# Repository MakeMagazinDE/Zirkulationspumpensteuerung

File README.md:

Maker Media GmbH

# Warmwasser-Sparpumpe

## für Heizkessel mit Zirkulationskreislauf

Heizkessel mit Brauchwasser-Erwärmung sind in der Regel mit einer Pumpe für den Warmwasser-Zirkulationskreislauf ausgerüstet, die regelmäßig anspringt, damit auch an entfernten Zapfstellen stets heißes Wasser entnommen werden kann. Diese Komfort-Funktion spart zwar Wasser, verbraucht aber unnötig Energie. Unsere Spar-Schaltung reduziert die Verschwendung auf ein Minimum.

## Stückliste

* C1:                  100uF/10V                                                    
* ESP-12E/F:           ESP8266-Board oder Wemos D1 Mini                                               
* F1:                  Sicherung 1,5A                                               
* JP1:                 3-Pin-Header RM 2.54mm für Temp.Sensor Dallas DS18B20        
* JP2:                 10-Pin-Header RM 2.54mm für Prog-Schnittstelle               
* PRINTTRAFO3.3V, 3W:  AC/DC-Wandler Meanwell IRM-01-3.3 oder ähnlich, 3,3V/1A      
* R1:                  1,5K                                                         
* R2:                  2,2K                                                         
* R3, R4:              10K                                                                                                               
* SSR__OMRONG3MB-202P: S102S02 SSR Solid State Relay                                
* VAR1:                VARISTOR 250V AC (optional)                                                 
* X1:                  Steckverbinder Phoenix MKDSN1,5/3-5,08   
* Schalterdose Feuchtraum
* Ggf. Schukostecker/Kupplung

Die Schaltung kann problemlos auf einer Lochraster-Platine aufgebaute werden, wenn netzspannungsführende Leitungen min. 5mm Abstand untereinander und 10mm Abstand zur Niederspannungsseite aufweisen. Beachten Sie die einschlägigen VDE-Vorschriften. Bei der Verwendung eines "nackten" ESP8266-Moduls anstelle des mit Stiftleisten ausgestatteten Wemos-Moduls ist einer (ggf. selbstgefertigte) Platine nötig. Das Layout für den Editor EAGLE finden Sie im entsprechenden Unterordner.

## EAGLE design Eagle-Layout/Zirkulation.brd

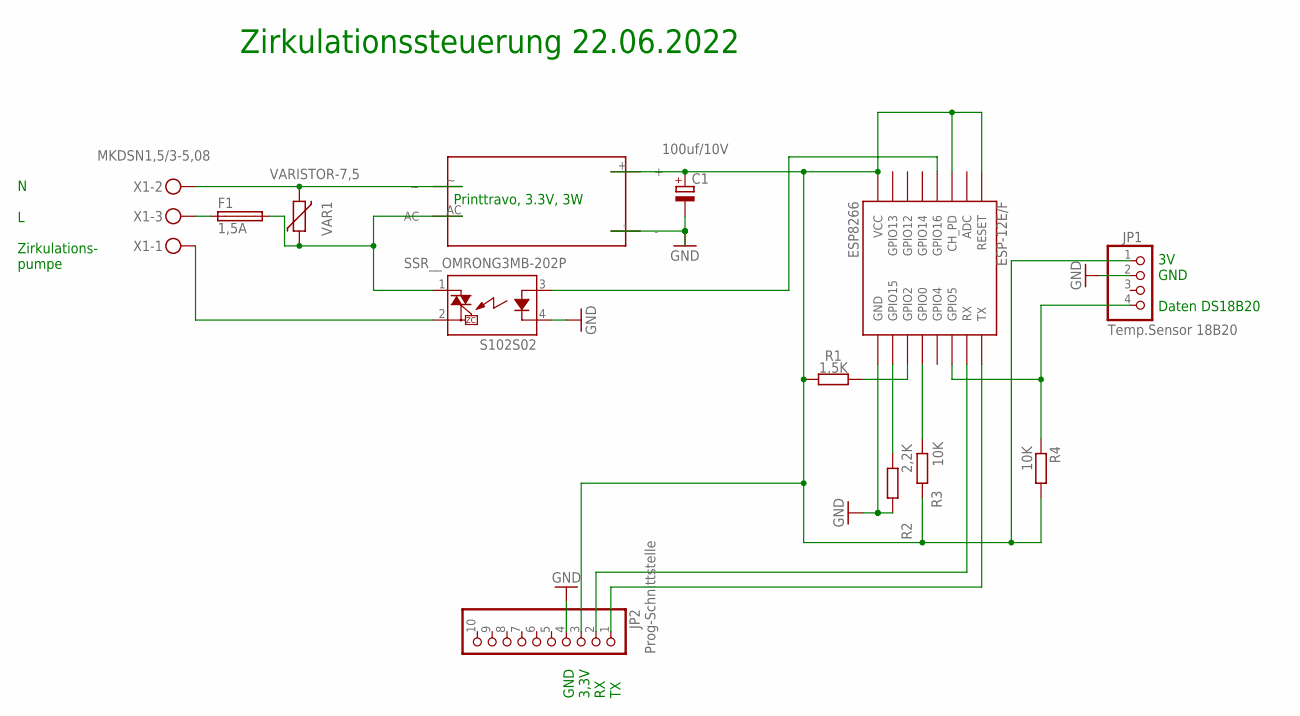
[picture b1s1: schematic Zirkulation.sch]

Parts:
C1: 100uf/10V; E2,5-7
ESP-12E/F: ESP8266; ESP12-SMD
F1: 1,5A; LITTLEFUSE
JP1: Temp.Sensor 18B20; 1X04
JP2: Prog-Schnittstelle; 1X10
PRINTTRAFO3.3V,_3W: PRINTTRAFO
R1: 1,5K; 0204/7
R2: 2,2K; 0204/7
R3, R4: 10K; 0204/7
SSR__OMRONG3MB-202P: S102S02; S202S02
VAR1: VARISTOR-7,5; R-7,5
X1: MKDSN1,5/3-5,08

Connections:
3.3V: C1.+, ESP-12E/F.CH_PD, ESP-12E/F.RESET, ESP-12E/F.VCC, JP1.1, JP2.3, PRINTTRAFO3.3V,_3W.+, R1.2, R3.2, R4.2
GND: C1.-, ESP-12E/F.GND, JP1.2, JP2.4, PRINTTRAFO3.3V,_3W.-, R2.1, SSR__OMRONG3MB-202P.4 (K)
GPIO0: ESP-12E/F.GPIO0, R3.1
GPIO2: ESP-12E/F.GPIO2, R1.1
GPIO5: ESP-12E/F.GPIO4 (GPIO5), JP1.4, R4.1
GPIO15: ESP-12E/F.GPIO15, R2.2
GPIO16: ESP-12E/F.GPIO16, SSR__OMRONG3MB-202P.3 (A)
L: F1.1, X1.3
L1: SSR__OMRONG3MB-202P.2 (DS2), X1.1
L_: F1.2, PRINTTRAFO3.3V,_3W.AC, SSR__OMRONG3MB-202P.1 (DS1), VAR1.1
N: PRINTTRAFO3.3V,_3W.~, VAR1.2, X1.2
RX: ESP-12E/F.RXD0 (RX), JP2.2
TX: ESP-12E/F.TXD0 (TX), JP2.1

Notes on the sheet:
Printtravo, 3.3V, 3W
N L Zirkulations- pumpe
Zirkulationssteuerung 22.06.2022
3V GND Daten DS18B20
GND 3,3V RX TX

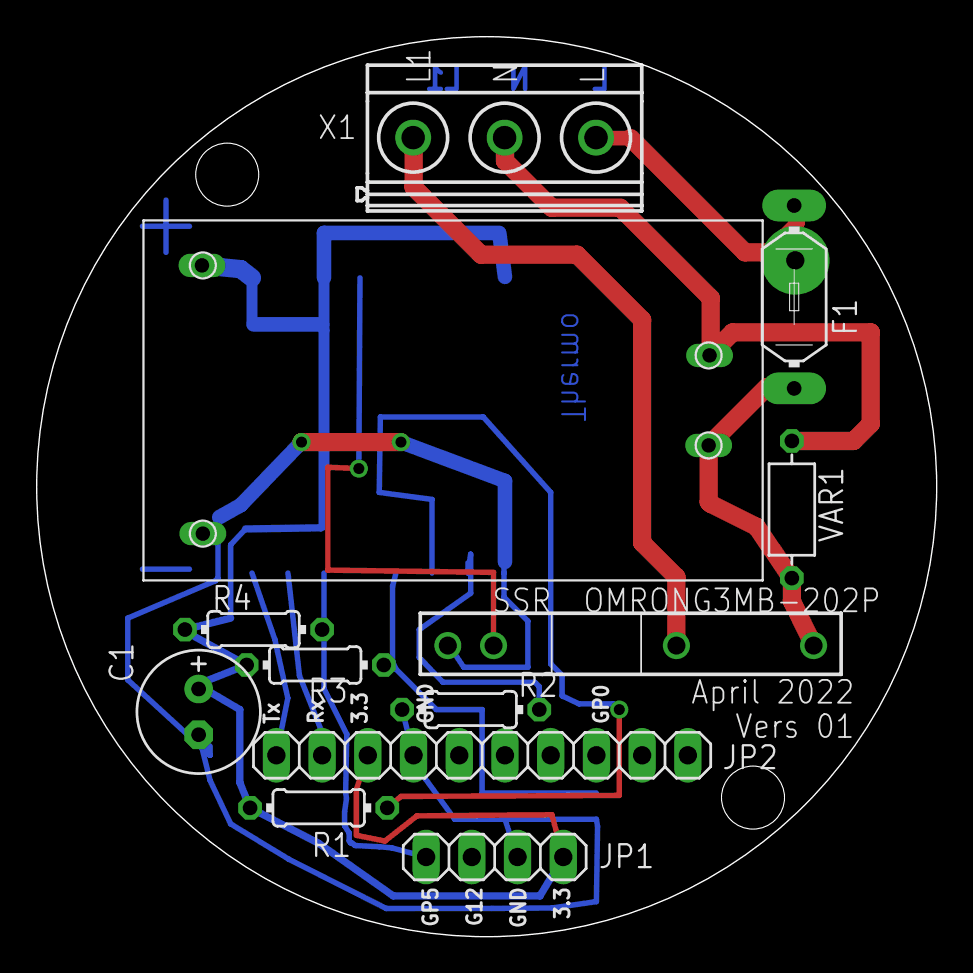
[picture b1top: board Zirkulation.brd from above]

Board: 2 copper layers, 50.0 x 50.0 mm, 13 parts (1 on the bottom side), 13 nets.

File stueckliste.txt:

Partlist

Exported from MQTT-Zirkulation.sch at 22.06.2022 13:15

EAGLE Version 9.6.2 Copyright (c) 1988-2020 Autodesk, Inc.

Assembly variant: 

Part                Value              Device          Package         Library         Sheet

C1                  100uf/10V          CPOL-EUE2.5-7   E2,5-7          rcl             1
ESP-12E/F           ESP8266            ESP12SMD        ESP12-SMD       esp8266modules  1
F1                  1,5A               LITTLEFUSE      LITTLEFUSE      fuse            1
JP1                 Temp.Sensor 18B20  PINHD-1X4       1X04            pinhead         1
JP2                 Prog-Schnittstelle PINHD-1X10      1X10            pinhead         1
PRINTTRAFO3.3V,_3W  PRINTTRAFO         PRINTTRAFO      PRINTTRAFO      Uwes_lib        1
R1                  1,5K               R-EU_0204/7     0204/7          rcl             1
R2                  2,2K               R-EU_0204/7     0204/7          rcl             1
R3                  10K                R-EU_0204/7     0204/7          rcl             1
R4                  10K                R-EU_0204/7     0204/7          rcl             1
SSR__OMRONG3MB-202P S102S02            S102S02         S202S02         relay           1
VAR1                VARISTOR-7,5       VARISTOR-7,5    R-7,5           varistor        1
X1                  MKDSN1,5/3-5,08    MKDSN1,5/3-5,08 MKDSN1,5/3-5,08 con-phoenix-508 1
